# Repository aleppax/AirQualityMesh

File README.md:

# outdoor air quality station 

current development status: [Proof of Concept.](roadmap.md)

IoT system monitoring outdoor air quality with multiple stations, remote data collection and analytics.
It can work both as a stationary or a roving unit, logging datetime, position and sensor data.

## Supported sensors 

|sensor| description | physical dimensions| max connected sensors |
|--|--|--|--|
| pms5003 | PM Sensor PMS5003 | pm1.0 pm2.5 | 2 |
| pms5003T | PM Sensor PMS5003T | pm1.0 pm2.5 humidity temperature | 2 |
| sngcja5 | PM Sensor SN-GCJA5 | pm1.0 pm2.5 | 1 |
| sps30 | PM Sensor SPS30 | pm1.0 pm2.5 | 1 |
| bmp280 | Pressure sensor BMP280 | barometric pressure | 1 |
| aht20 | Humidity and Temperature Sensor AHT20 | humidity temperature | 1 |

* there is an overall max number of 2 connected PM sensors at the same time, regardless of the model. The limit is software, therefore it can be overcome.

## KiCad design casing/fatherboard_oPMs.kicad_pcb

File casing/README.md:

## PCB

The PCB design is single sided, has no SMD parts and a minimalistic BOM. Components are on the opposite side of the copper layer. 
Hence it is very straightforward to make it at home both with a CNC or chemicals. 
The main purpose of the PCB is to speed up the assembly but it is better to choose 
terminals that guarantee contact continuity over time since this is an outdoor application partially exposed to weather conditions.
The two resistors are 20K and 30K Ohm, they are used as an external voltage divider to measure the battery voltage. 
We decided to avoid using the internal ADC3 with its own voltage divider because this relies on the WL_GPIO2 of the wireless chip and we didn't want conflicts during wifi communication. If a good precision isn't paramount it is possible to stop using the external circuit in favor of the builtin one.

The connection PCB has been designed so that half of the Raspberry Pico, the part where the antenna is located, protrudes, so as to move connection wires and tracks away as far as possible from the transceiver area.

## Case

the casing is designed to be composed mainly of cheap parts available from electrical component suppliers, for which a compact junction box was chosen (150 X 110 X 70 mm, IP 56), commercially available air vents (to which a double layer of mosquito netting was added for greater protection from small insects). Each air vent has an overall opening of 8 cm^2.

## Solar panel

The solar panel (Cellevia CL-SM3P) is extremely cheap but still slightly oversized, it has the secondary function of protecting the casing from direct solar radiation and has an aluminum frame for easier fixing.

## Fixing 

A sturdy joint plate with screws and nuts for fixing to a post or railing or fence. Different fixing systems will have to be studied according to the location.

## Sensor holder

The only customized component is the sensor fixing structure which allows to house two particulate sensors and possibly a humidity and temperature sensor. Subsequent redesigns could accommodate a small fan in case it is necessary to force a greater air exchange.

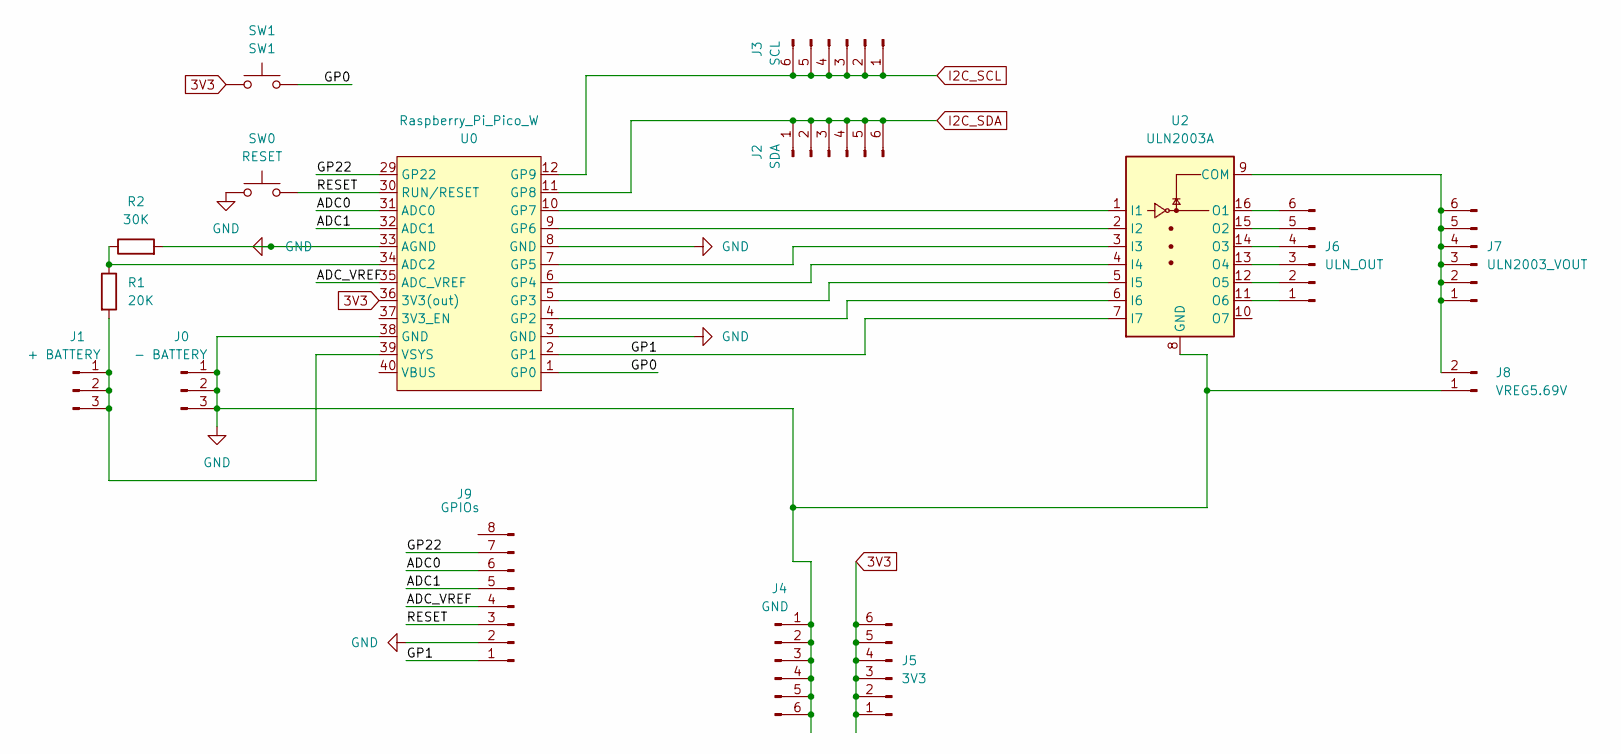
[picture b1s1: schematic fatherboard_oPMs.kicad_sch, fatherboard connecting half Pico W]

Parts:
J0: - BATTERY; PinHeader_1x03_P2.54mm_Vertical
J1: + BATTERY; PinHeader_1x03_P2.54mm_Vertical
J2: SDA; PinHeader_1x06_P2.54mm_Vertical
J3: SCL; PinHeader_1x06_P2.54mm_Vertical
J4: GND; PinHeader_1x06_P2.54mm_Vertical
J5: 3V3; PinHeader_1x06_P2.54mm_Vertical
J6: ULN_OUT; PinHeader_1x06_P2.54mm_Vertical
J7: ULN2003_VOUT; PinHeader_1x06_P2.54mm_Vertical
J8: VREG5.69V; PinHeader_1x02_P2.54mm_Vertical
J9: GPIOs; PinHeader_1x07_P2.54mm_Vertical
R1: 20K; R_Axial_DIN0207_L6.3mm_D2.5mm_P7.62mm_Horizontal
R2: 30K; R_Axial_DIN0207_L6.3mm_D2.5mm_P7.62mm_Horizontal
SW0: RESET; SW_PUSH_6mm_H5mm
SW1: SW1; SW_PUSH_6mm_H5mm
U0: Raspberry_Pi_Pico_W; DIP_Socket-24_W11.9_W12.7_W15.24_W17.78_W18.5_3M_224-1275-0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
U2: ULN2003A; DIP-16_W7.62mm

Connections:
3V3: J5.1, J5.2, J5.3, J5.4, J5.5, J5.6, SW1.1, U0.36 (3V3(out))
/ADC0: J9.6, U0.31 (ADC0)
/ADC1: J9.5, U0.32 (ADC1)
/ADC_VREF: J9.4, U0.35 (ADC_VREF)
/GP0: SW1.2, U0.1 (GP0)
/GP1: J9.1, U0.2 (GP1), U2.7 (I7)
/GP22: J9.7, U0.29 (GP22)
/RESET: J9.3, SW0.2, U0.30 (RUN/RESET)
GND: J0.1, J0.2, J0.3, J4.1, J4.2, J4.3, J4.4, J4.5, J4.6, J8.1, J9.2, R2.2, SW0.1, U0.3 (GND), U0.8 (GND), U0.33 (AGND), U0.38 (GND), U2.8 (GND)
I2C_SCL: J3.1, J3.2, J3.3, J3.4, J3.5, J3.6, U0.12 (GP9)
I2C_SDA: J2.1, J2.2, J2.3, J2.4, J2.5, J2.6, U0.11 (GP8)
unnamed: J1.1, J1.2, J1.3, R1.2, U0.39 (VSYS)
unnamed: J6.1, U2.11 (O6)
unnamed: J6.2, U2.12 (O5)
unnamed: J6.3, U2.13 (O4)
unnamed: J6.4, U2.14 (O3)
unnamed: J6.5, U2.15 (O2)
unnamed: J6.6, U2.16 (O1)
unnamed: J7.1, J7.2, J7.3, J7.4, J7.5, J7.6, J8.2, U2.9 (COM)
unnamed: R1.1, R2.1, U0.34 (ADC2)
unnamed: U0.4 (GP2), U2.6 (I6)
unnamed: U0.5 (GP3), U2.5 (I5)
unnamed: U0.6 (GP4), U2.4 (I4)
unnamed: U0.7 (GP5), U2.3 (I3)
unnamed: U0.9 (GP6), U2.2 (I2)
unnamed: U0.10 (GP7), U2.1 (I1)

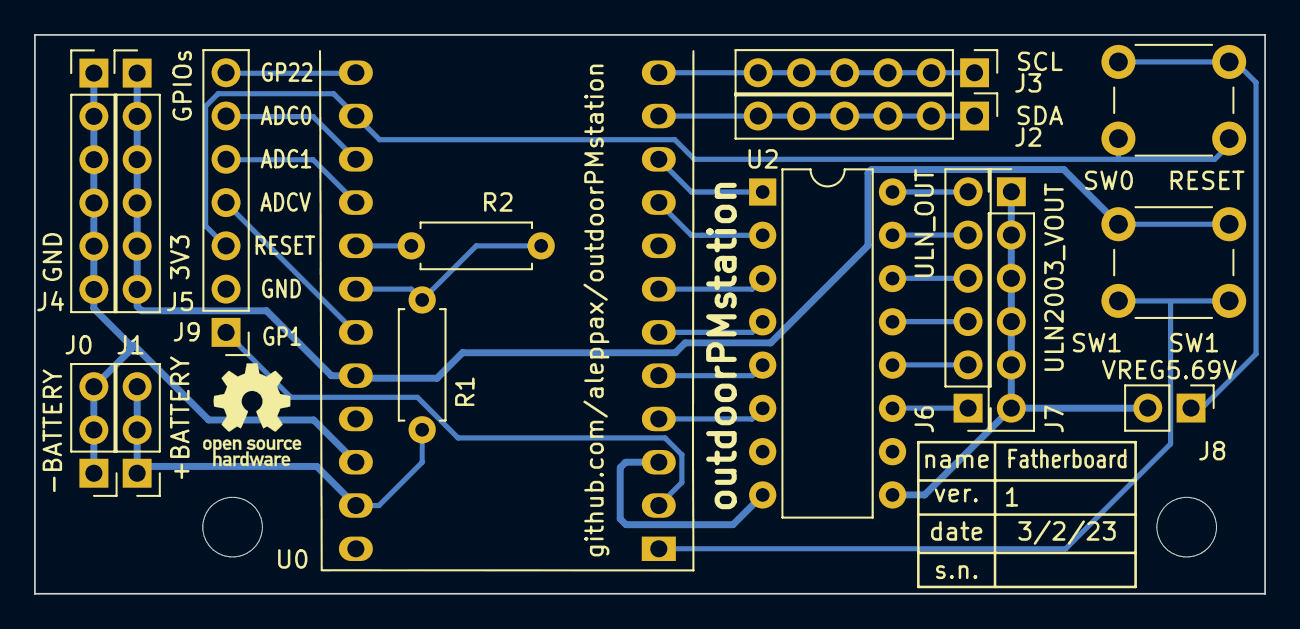
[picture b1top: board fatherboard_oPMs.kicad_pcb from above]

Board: 2 copper layers, 72.2 x 32.8 mm, 16 parts (0 on the bottom side), 26 nets.

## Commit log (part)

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2022-12-17 Create BOM.md
    added stripped down BOM for the alpha development stage.
2022-12-17 added basic folder structure
2022-12-28 added geolocation details to the configuration form
2023-01-13 added basic battery monitor, scheduler and bmp180 library
2023-01-14 added status monitoring
2023-01-17 initial breadboard layout of the main components
2023-01-18 first revision of the sensors holder
2023-02-03 layout replaced by new pcb design
2023-02-03 rendering
2023-02-10 removed external ntp library, used internal. added some settings related to the connection layout.
2023-02-12 first attempt to provide a basic automatic update method OTA
2023-02-12 hardcoding version file name, in micropython I don't know a way to import a modlue whose name can change
2023-02-13 adopted SPS30 library
2023-02-13 Add files via upload
    some pictures of the prototype
2023-02-13 Add files via upload
    solar panel
2023-02-13 Update README-casing.md
    added another picture
2023-02-13 Update BOM.md
    updated BOM
2023-02-15 added resilient softsleep functionality
2023-02-17 steps towards a working routine with all functionality. lightsleep,updates,measurements and datalogging
2023-02-18 rotating log files
2023-02-18 created log directory
2023-02-18 removed system.log
2023-02-18 database structure
2023-02-18 bug with variable name
2023-02-20 prova colori
2023-02-20 picture of the first batch of PCB
2023-02-22 data fields in ordered dict
2023-02-23 added sleep function with wdt feeder
2023-02-23 bug float to int conversion
2023-02-23 imported filelogger
2023-02-23 probably fixed another slip
2023-02-23 Revert "dealing with a few exceptions" only to try a revert This reverts commit ec9d8df3b9fd4c3c7aeeb8ab3cb702f5b2b5fa9a.
2023-02-23 dealing with a couple of exceptions
2023-02-25 push per save20230225
2023-02-25 main.py di base
2023-02-25 missing import, new i2c bus speed setting
2023-02-26 an external photo of the installed system
2023-02-26 "a closeup of the installer's little helper"
2023-02-27 Update README.md
    showing current progress
2023-02-27 new low power mode when battery is low. enabled logging data to file when online datalogger fails adapted sensor library
2023-02-28 averaging n measures for each sensor, simpler wakeup cycle, switching off sensors there was a problem with I2C when I tried to gently disable the sensor SPS30, therefore the working solution is to dr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
    now config has two new settings:
    sensors = {
    'average_particle_measurements' : 20,
    'average_measurement_interval_ms' : 1000,
    }
    to determine the timespan and the number of measurements used to get an average
2023-02-28 sometimes the WDT can't wait enough
2023-02-28 a small delay was missing before starting sps30 sensor
2023-02-28 added simplicistic data sender
2023-03-01 fixed many errors, first success test with online server
2023-03-02 allineamento su base_a (ma bypass ULM e Vdd diretta da piedino 39)
2023-03-02 config con picosps30 (prove se serve su i2c_1) e nuova sezione scheduler
2023-03-02 umqtt_simply added
2023-03-02 pulizia, ribasamento e rimozione files di prova
2023-03-03 aggiunta verifica getstation prima di scrivere measurements
2023-03-04 ntp update was used the wrong way. There were still cases of system hangout due to NTP failing to sync time. It is preferable to let the wdt to reboot the system instead of continuing without the cor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
2023-03-05 added initial MQTT sending routine
2023-03-05 reinsert client_ID
2023-03-05 update mqtts.yaml per fix nome variabili
2023-03-06 restructured main.py, anticipating updates, modified mqtt, removed internal development comments added comments to main
2023-03-07 rebased snippets used to add autocleaning routine to SPS30 sensor
2023-03-07 added timeout to datalogger post request to avoid wdt intervention
2023-03-07 fixed datalogger
2023-03-08 add file HA
2023-03-08 prova rapida ok, tutto come branch base, mqttlogger ok , ma loop non mi va
2023-03-08 fixed scope error, after code moved inside module
2023-03-08 battery cherge level is increased to 4,95V
2023-03-08 compensate time elapsed during deepsleep
2023-03-08 DEEPSLEEP_RESET do not exists for the pico
2023-03-08 missing update_NTP status change
2023-03-08 old unused variable removed
2023-03-09 moving around function calls_2
2023-03-11 separate cycle for auxiliary PM sensor the battery requirement halves.
2023-03-11 modified battery limits
2023-03-14 Update roadmap.md
    More details about the roadmap
2023-03-14 connect to wifi only if update is scheduled, other power optimizations
2023-03-14 enabled scheduled data submission
2023-03-14 reverting separate sensor usage because the I2C bus can't be used anyway in a separate manner
2023-03-14 fixed use of global variable, pause between one submission and another
2023-03-14 missing readlines() in filelogger read function!
2023-03-15 fixed #32 didn't realize that was passing a pointer instead of instantiating a copy
2023-03-16 removed use of wifi enable pin 23
2023-03-16 save programma che gira da un'ora
2023-03-17 changed barometric pressure units to something more common
2023-03-17 system can't continue if time isn't up to date, rebooting
2023-03-21 trying to achieve a more accurate voltage reading
2023-03-21 file memory limit allocation
2023-03-22 further fixing memory usage
2023-03-22 Update cron.py
    Another test
2023-03-22 Update cron.py
    Step into config update
2023-03-22 Update cron.py
    filter dicts
2023-03-23 now the old config file is copied to configold.py before updating, then each setting which differs from the default is preserved
2023-03-23 salvo per prova i file di vscode
2023-03-23 reboot only if ntp fails. removed redundant log message
2023-03-24 missing condition led to not write new values into config file
2023-03-24 logging vsys voltage
2023-03-24 updated db structure adding voltage value
2023-03-29 swapped channels
    Swapped ch1 and ch 2 of pm sensor
2023-03-29 latest_aux_measure variable changed name
2023-03-29 implicit reload of config module vhen adding/updating a key/value
2023-03-29 avoiding errors when no sensor is connected and all values are zero, than calculating the dew point results in an error trying to solve log(0) Caution: the value of the class name of module ahtx0 has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
2023-04-01 added error handling when connection drops and datalogger can't send data
2023-04-01 insert maximum value for keepalive in mqtt
2023-04-02 submission in chunks of data but saving those singular lines that failed to arrive to the server
2023-04-03 fixed
2023-04-03 Update config.py
    missed a few modifications
2023-04-03 added version file
2023-04-04 minor fixes
2023-04-04 removed messages from schedule functions
2023-04-06 importing function freq
2023-04-07 save per prove opmsmap in server dir
2023-04-08 battery measurement is done before anithing else
2023-04-14 Update main.py
    Moved sensors.shutdown() inside sensors.measure()
2023-04-14 Update sensors.py
    Moved sensors shutdown inside measure
2023-04-15 loosen the criteria for considering the low power phase over
2023-04-16 Update sps30.py
    Sps30 to channel 1
2023-04-18 fixed error of memory exhausted when using urequests
2023-04-18 linted. Left many warnings.
2023-04-21 trying to avoid errors when sending measurements to server. socket.settimeout seems to work on RP pico.
2023-04-21 added second attempt to send each record, added more log messages
2023-04-25 filter log levels, minor changes
2023-04-25 modified max number of times we attempt to send measures
2023-04-26 updated version
2023-04-27 added patched firmware for raspberry pico W, patch from https://github.com/micropython/micropython/pull/10803
2023-04-27 Update filelogger.py
    Replaced print statement with logger function
2023-04-28 save measures as soon as possible
2023-04-29 used different variable names between different modules, just in case... added more logging to understand why lines not sent are not written back to file.
2023-04-29 version 56
2023-04-29 version
2023-05-02 Update version.py
    disnable_sensors will persist after update but will not be used anymore
2023-05-07 mor logs. There is a problem with the measurement phase, the system halts unexpectedly and the wdt restarts
2023-05-09 sending all data in a single post transaction
2023-05-11 added erroe handling in case of timeout of file download
2023-05-11 resolve diffs
2023-05-11 restoring references to mip protected functions
2023-05-11 fixed some bugs in cron.py after code restructuring
2023-05-11 many fixes wdt function name has changed
2023-05-12 Update filelogger.py
    not using readiness for more efficiency
2023-05-12 Update version.py
    removed readlines and updated version to 62
2023-05-12 testing a version which restarts wlan connection if first sending attempt fails
2023-05-13 ruff
2023-05-15 simplified reply parsing
2023-05-20 added precompiled firmware with micropython PR #8968, just in case someone would try to test it. Two small but important edits: datalogger should use unsecure http for two reasons: the micropython im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
2023-05-21 separate bytecode version
2023-06-03 web interface inproved
2023-06-05 improved AP configuration page, using microdot library.
2023-06-07 cosmetic change
2023-06-07 minor change
2023-06-07 station UID
2023-06-09 completed the client side of the interactive configuration
2023-06-13 from one single html file to separate files in order to avoid problems of ram allocation
2023-06-14 completed the code to save settings in config.py from webconfig pages
2023-06-14 new version with working webconfig micropython server
2023-06-15 created makefile to spped up the compilation to bytecode of micropython code. It requires a built micropython cross compiler in the directory ../micropython/mpy-cross/build/mpy-cross
2023-06-15 added restart button to webconfig, disabled WDT during wireless configuration
2023-06-15 fixed css rule
2023-06-20 ignored backup
2023-06-21 mirrored to dist folder
2023-06-21 renamed folders, compiled binaries
2023-06-21 fixed path
2023-06-21 removed service file
2023-06-23 edited marker and possible logo
2023-06-23 Update README.md
    added marker
2023-06-24 adding sensor PMS5003 with UART communication
2023-06-24 more resilient logic, completed implementation behind main PM sensor and auxiliary ones: if a sensor is the main sensor, data are saved to 'pm2.5' and 'pm1.0', if it is auxiliary, data are saved to '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
2023-06-24 added possibility to connect two PMS5003 to different UART pins
2023-06-25 fixed errors while working with two pms5003
2023-06-25 fixed key name in dict
2023-06-25 correct scale of measurement for temperature and humidity of pms5003
2023-07-01 added LED signalling functionality started designing the web map, currently still WIP
2023-07-03 chart updates when switching from one marker to another
2023-07-04 updated picture
2023-07-04 Update README.md
    relative path
2023-07-07 data visualization improvements
2023-07-07 Update README.md
    added picture of data map
2023-07-13 legend
2023-07-14 utility file per recupero measures da file measure.txt
2023-07-22 moved to base_rob
    moved to base_rob
2023-07-27 added logic switching between rover mode and station mode
2023-07-28 finished basic rover functionality
2023-07-29 saving location data to measures
2023-08-07 adding neo6m config
2023-09-29 added compiled sources
2023-09-29 preview of the onboard configuration web server
2023-09-30 opensensemap setting configuration via embedded webserver added 3d model of GPS enclosure
2023-10-01 removed file
2023-10-07 version number
2023-10-07 still some fixes
2023-10-21 fixed web interface listing sensors
2023-12-29 reverted the change in _reload function since it is still required to reload each instance of config module after it is modified
2024-02-12 Update README.md
    renamed project to Air Quality Mesh
2024-02-13 Update config.py
    git path
2024-02-13 added max-height to legend
2024-02-15 added a button to scroll the chart backward in time
